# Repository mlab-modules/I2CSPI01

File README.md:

# I2CSPI01 - I2C to SPI bridge

The I2CSPI01 module is designed for systems where a microcontroller with only an I2C interface needs to communicate with one or more SPI peripherals. It acts as a bridge that translates I2C commands into SPI signals, allowing integration of SPI devices such as ADCs, DACs, memory chips, or sensors into an I2C-based architecture. This simplifies wiring and reduces the number of required signals.

## Features

* I2C to SPI bridge based on SC18IS602B
* Supports up to four SPI slave devices
* Unused chip-select pins configurable as GPIO
* SPI clock modes: 0, 1, 2, 3
* SPI speed configurable: 58 kHz to 1.843 MHz
* GPIOs support multiple modes: quasi-bidirectional, push-pull, input-only, open-drain
* 200-byte internal buffer
* Operates as I2C slave and SPI master
* 3.3V supply voltage

## Specifications

| Parameter    | Value                                      |
| ------------ | ------------------------------------------ |
| Power Supply | Max. 3.6 V                                 |
| Dimensions   | 40.13 x 30.00 x 16 mm                      |
| Interface    | I2C (up to 400 kHz), SPI (up to 1.843 MHz) |
| IC Used      | SC18IS602B                                 |

## Assembly Notes

* One via must be drilled due to a PCB short.
* J5 header is not functional due to PCB layout issue.

## Resources

* [SC18IS602B Datasheet](https://www.nxp.com/docs/en/data-sheet/SC18IS602B.pdf)
* [Buy from UST](https://www.ust.cz/about/)

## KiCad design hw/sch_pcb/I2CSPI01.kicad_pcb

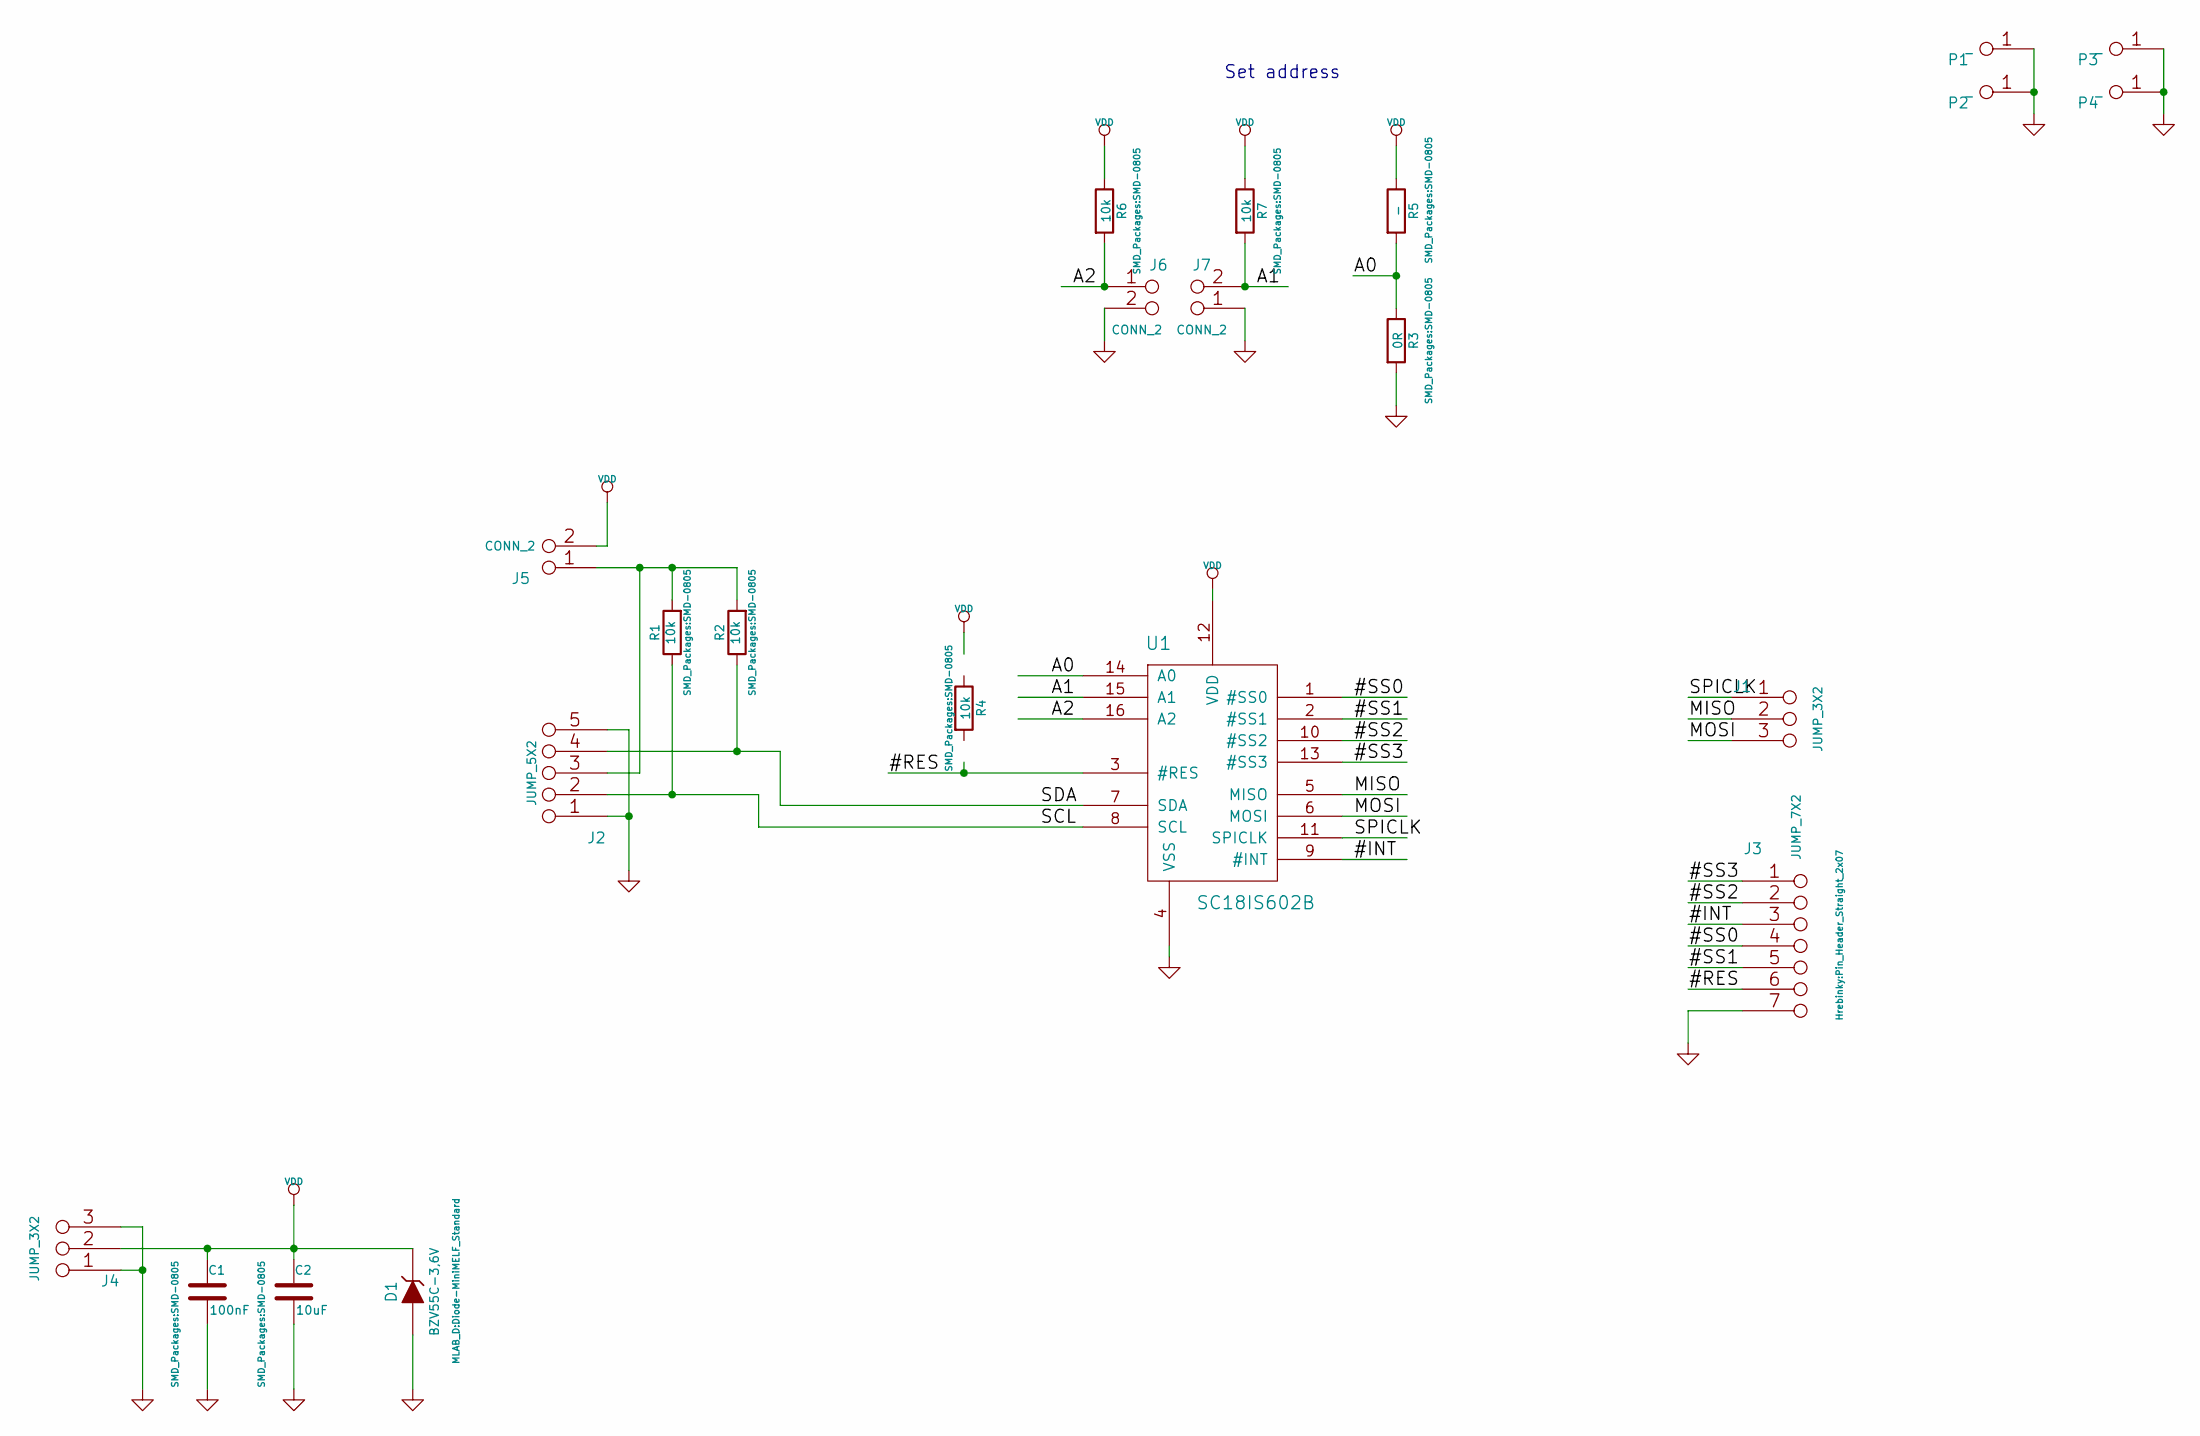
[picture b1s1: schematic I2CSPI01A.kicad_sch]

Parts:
C1: 100nF; SMD-0805
C2: 10uF; SMD-0805
D1: BZV55C-3,6V; Diode-MiniMELF_Standard
J1, J4: JUMP_3X2; Pin_Header_Straight_2x03
J2: JUMP_5X2; Pin_Header_Straight_2x05
J3: JUMP_7X2; Pin_Header_Straight_2x07
J5, J6, J7: CONN_2; Pin_Header_Straight_1x02
P1, P2, P3, P4: _; MountingHole_3mm
R1, R2, R4, R6, R7: 10k; SMD-0805
R3: 0R; SMD-0805
R5: -; SMD-0805
U1: SC18IS602B; TSSOP-16

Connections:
/#INT: J3.3, J3.12, U1.9 (#INT)
/#RES: J3.6, J3.9, R4.2, U1.3 (#RES)
/#SS0: J3.4, J3.11, U1.1 (#SS0)
/#SS1: J3.5, J3.10, U1.2 (#SS1)
/#SS2: J3.2, J3.13, U1.10 (#SS2)
/#SS3: J3.1, J3.14, U1.13 (#SS3)
/A0: R3.1, R5.2, U1.14 (A0)
/A1: J7.2 (PM), R7.2, U1.15 (A1)
/A2: J6.1, R6.2, U1.16 (A2)
/MISO: J1.2 (1), J1.5, U1.5 (MISO)
/MOSI: J1.3, J1.4, U1.6 (MOSI)
/SCL: J2.2, J2.9, R1.1, U1.8 (SCL)
/SDA: J2.4, J2.7, R2.1, U1.7 (SDA)
/SPICLK: J1.1, J1.6, U1.11 (SPICLK)
GND: C1.2, C2.2, D1.1 (A), J2.1, J2.5, J2.6, J2.10, J3.7, J3.8, J4.1, J4.3, J4.4, J4.6, J6.2 (PM), J7.1, P1.1, P2.1, P3.1, P4.1, R3.2, U1.4 (VSS)
unnamed: J2.3, J2.8, J5.1, R1.2, R2.2
VDD: C1.1, C2.1, D1.2 (K), J4.2 (1), J4.5, J5.2 (PM), R4.1, R5.1, R6.1, R7.1, U1.12 (VDD)

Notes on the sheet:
Set address

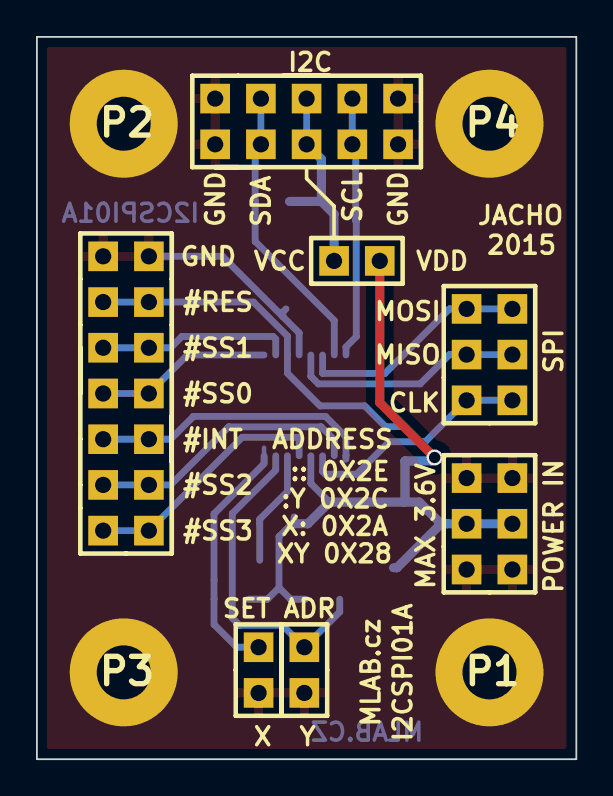
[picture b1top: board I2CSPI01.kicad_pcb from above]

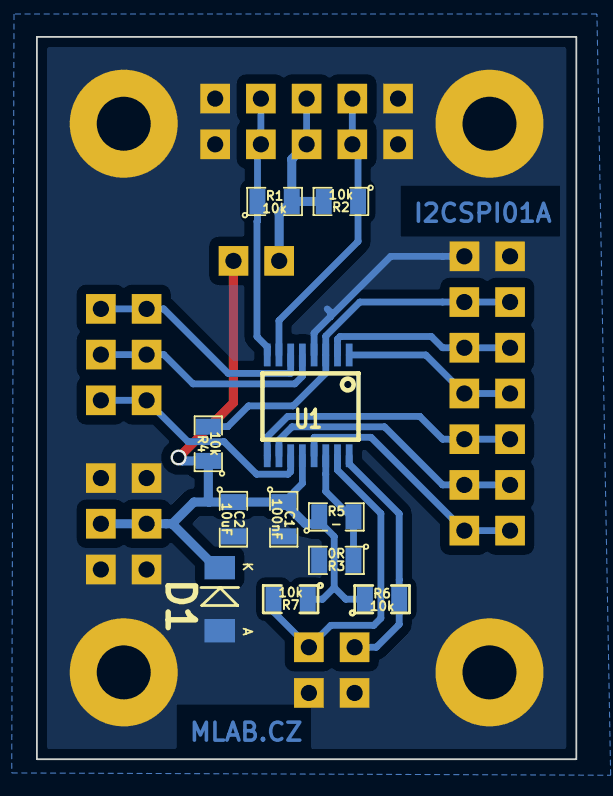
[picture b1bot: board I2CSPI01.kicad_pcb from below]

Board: 2 copper layers, 30.0 x 40.1 mm, 22 parts (11 on the bottom side), 17 nets.

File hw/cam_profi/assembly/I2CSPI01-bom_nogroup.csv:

Component,Description,Part,References,Value,Footprint,Quantity Per PCB,Datasheet
1,,C_3,C1,100nF,SMD-0805,1,
2,,C_4,C2,10uF,SMD-0805,1,
3,,ZENER_2,D1,"BZV55C-3,6V",Diode-MiniMELF_Standard,1,
4,,CONN_2_6,J5,CONN_2,Pin_Header_Straight_1x02,1,
5,,CONN_2_4,J6,CONN_2,Pin_Header_Straight_1x02,1,
6,,CONN_2_5,J7,CONN_2,Pin_Header_Straight_1x02,1,
7,,JUMP_3X2_3,J1,JUMP_3X2,Pin_Header_Straight_2x03,1,
8,,JUMP_3X2_4,J4,JUMP_3X2,Pin_Header_Straight_2x03,1,
9,,JUMP_5X2_2,J2,JUMP_5X2,Pin_Header_Straight_2x05,1,
10,,JUMP_7X2_2,J3,JUMP_7X2,Pin_Header_Straight_2x07,1,
11,,R_14,R3,0R,SMD-0805,1,
12,,R_10,R1,10k,SMD-0805,1,
13,,R_9,R2,10k,SMD-0805,1,
14,,R_8,R4,10k,SMD-0805,1,
15,,R_11,R6,10k,SMD-0805,1,
16,,R_12,R7,10k,SMD-0805,1,
17,,R_13,R5,-,SMD-0805,1,
18,,SC18IS602B_2,U1,SC18IS602B,TSSOP-16,1,

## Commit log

2017-08-22 rename category folders
2017-08-22 rename files and module folders
2017-08-22 change images path
2017-08-22 create hw folder
2017-08-22 change filepaths
2017-08-22 rm empty json html files, rename module.json files
2017-08-22 new .json files
2017-11-02 [MLABweb] 2017-11-02 00:09:53 I2CSPI01A
2018-11-05 Presun obrazku do slozky img. Pregenerovani dokumentaci.
2023-05-28 automated commit; add github actions
2023-05-28 Update workflow files
2023-05-28 Update metadata files
2023-07-05 automated commit; rename source files to new naming convence
2023-09-16 Update status
2025-08-19 Update KiCAD workflow and project data.
2025-08-19 Rename KiCAD project.
2025-08-19 Update actions products
2025-08-19 Improve readme.
